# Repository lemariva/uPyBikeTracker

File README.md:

# uPyBikeTracker

## Main Hardware Components
| Part  | Description |  Qty |
|-:|-:|-:|
| [Wemos ESP32 Lora Board](https://www.banggood.com/2Pcs-Wemos-TTGO-LORA32-868915Mhz-ESP32-LoRa-OLED-0_96-Inch-Blue-Display-p-1239769.html?p=QW0903761303201409LG) | ESP32 + SSD1306 + SX1276 + CP2102| x1 |
| [GPS NEO7M](https://www.banggood.com/Ublox-NEO-7M-Flight-Controller-GPS-Module-Built-in-Data-Memory-p-973621.html?p=QW0903761303201409LG) / [GPS NEO6M](https://www.banggood.com/GY-NEO6MV2-New-NEO-6M-GPS-Module-NEO6MV2-with-Flight-Control-EEPROM-MWC-APM2_5-Large-Antenna-p-1348935.html?p=QW0903761303201409LG) | GPS Module| x1|
|[MPU9250/5](https://www.banggood.com/MPU-9250-GY-9250-9-Axis-Sensor-Module-I2C-SPI-Communication-Board-For-Arduino-p-1227241.html?p=QW0903761303201409LG)| IMU 10DOF Sensor| x1 |
|[IRLML2502](https://www.ebay.de/itm/20PCS-IRLML2502-ORIGINAL-MOSFET-N-CH-20V-4-2A-SOT-23-/162711066575) | MOSFETs | x4 | 
|[BME680](https://www.banggood.com/CJMCU-680-BME680-BOSCH-Temperature-And-Humidity-Pressure-Sensor-p-1268323.html?p=QW0903761303201409LG)| Atmospheric Pressure Sensor| x 1|
|[BQ27510-G3](http://www.ti.com/product/bq27510-g3/description) | Fuel Gauge |x1|
|[Lipo-Battery](https://www.banggood.com/ZOP-Power-3_7V-850mAh-1S-25C-Lipo-Battery-p-1013586.html?p=QW0903761303201409LG)| Battery| x1|
|[RTC Clock](https://www.conrad.de/de/ds1339u-33-tr-rtc-clockcalendar-i2c-interface-msop8-800202661.html)| Clock| x1 |
|[CR1220](https://www.conrad.de/de/knopfzellenhalter-1-cr-1216-cr-1220-horizontal-oberflaechenmontage-smd-l-x-b-x-h-1892-x-1207-x-318-mm-keystone-300-651317.html)| Battery Socket| x1 |
|[SIL Socket Row Strip PCB Connector](https://www.banggood.com/5-Pair-40-Pin-2_54mm-Male-Female-SIL-Socket-Row-Strip-PCB-Connector-p-953486.html?p=QW0903761303201409LG)| SIL Socket Row Strip PCB Connector | x1|
|[SMD Tact Push Buttons](https://www.banggood.com/100pcs-3-x-6-x-2_5mm-DC-12V-0_5A-SMD-Tact-Push-Button-Switch-p-1202259.html?p=QW0903761303201409LG)| Buttons| x4|
|[bq51013B](http://www.ti.com/product/BQ51013B/technicaldocuments)|  Highly Integrated Wireless Receiver Qi| x1|

## More Info
More info coming soon on [lemariva.com](https://lemariva.com).

## Revision
* 1.3v added wireless charging (not revised yet)
* 1.2v breakout boards integrated to the main board
* 1.1v added RTC Clock (DS1339)
* 1.0v initial commit

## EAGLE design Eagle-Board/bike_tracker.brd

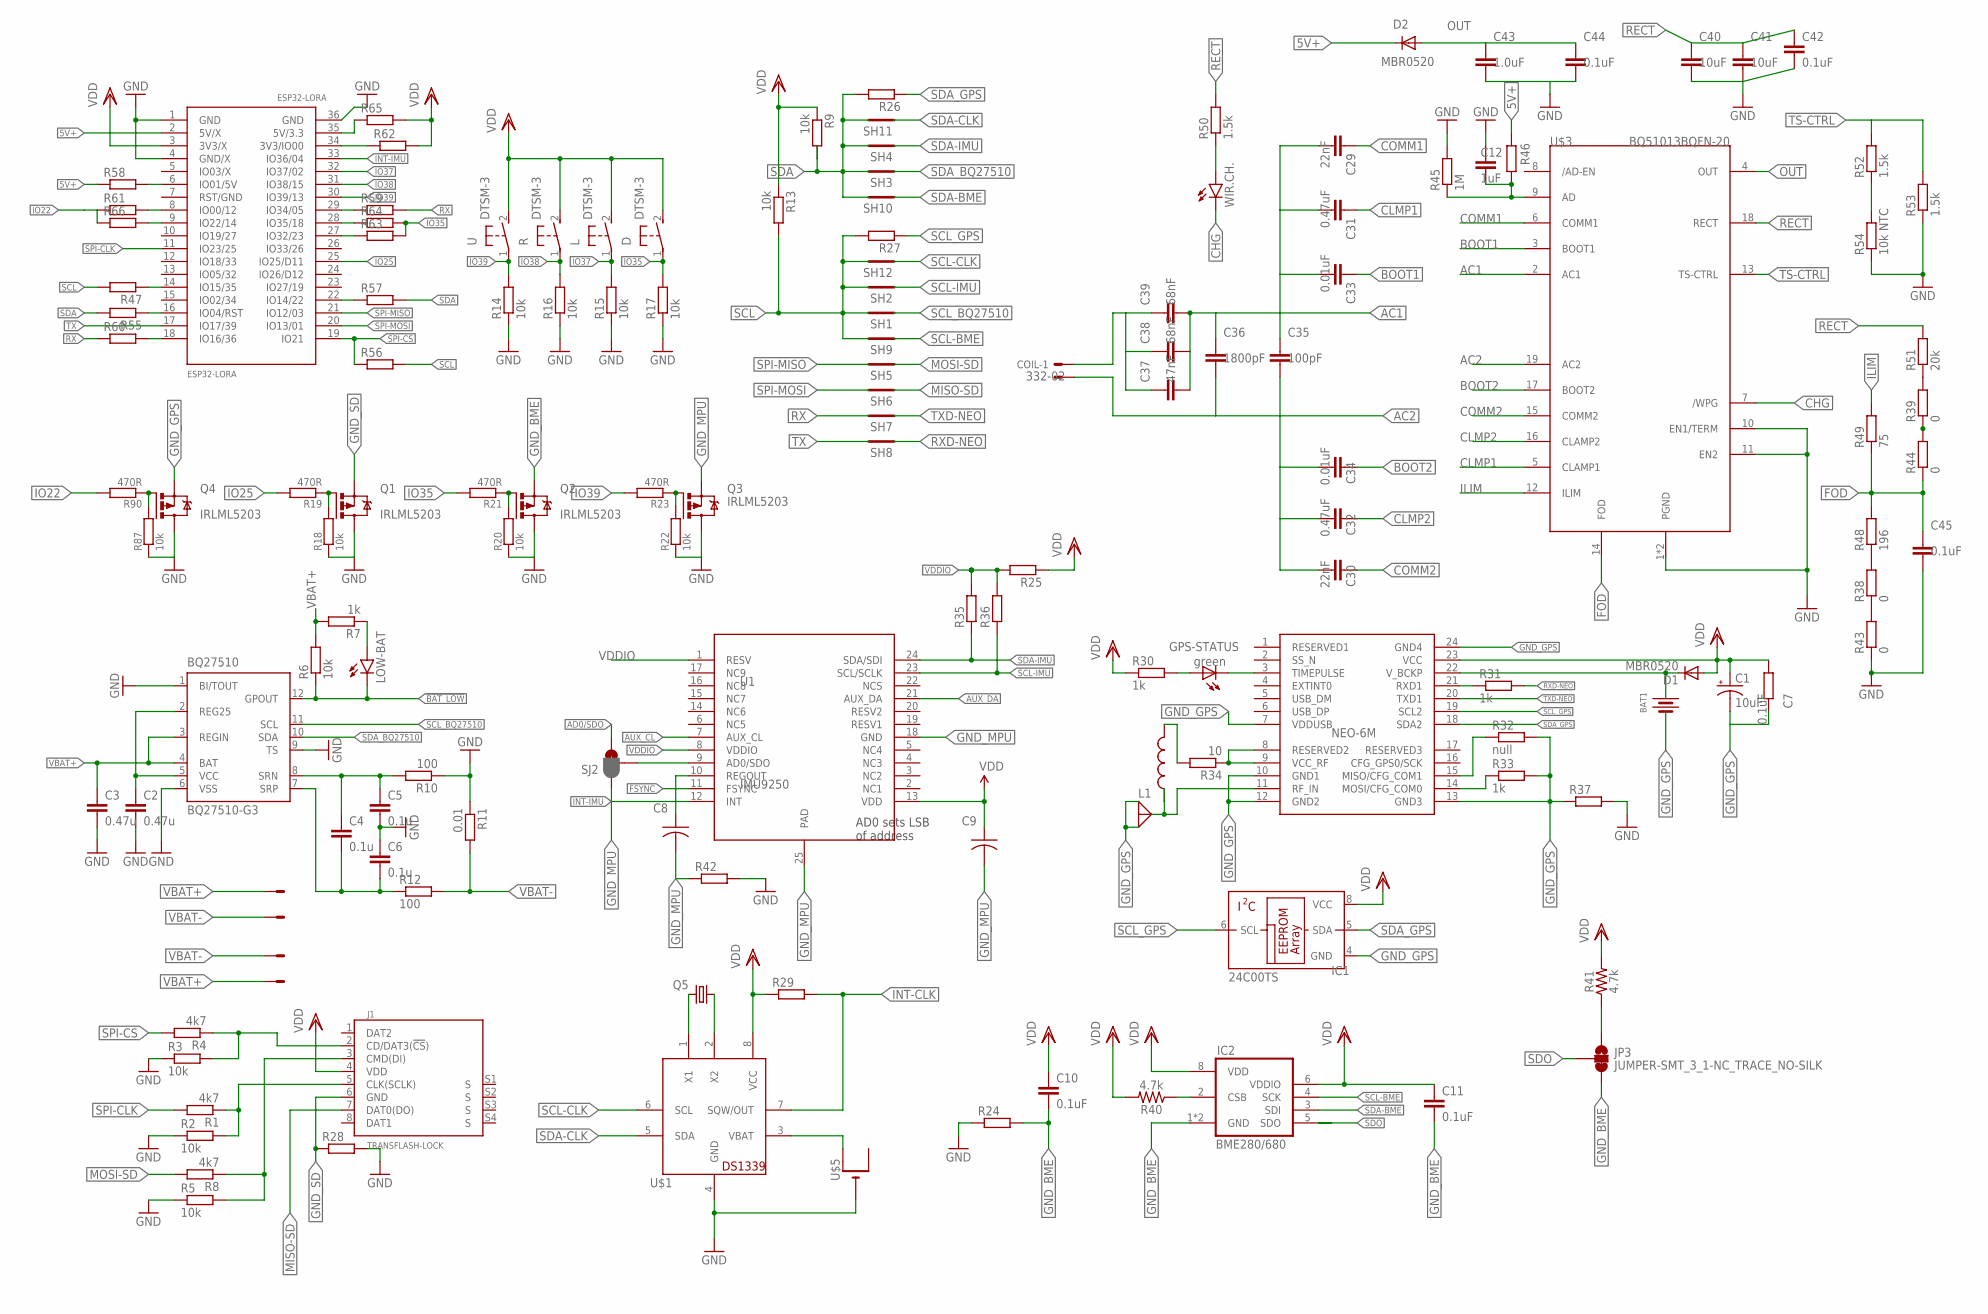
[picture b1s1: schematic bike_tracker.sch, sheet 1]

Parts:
BAT: 332-02
BAT1: XH414; TS414H
BAT-IN: 332-02
BQ27510: BQ27510-G3; DRZ
C1: 10uF; EIA3528
C2, C3: 0.47u; C0603
C4, C5, C6: 0.1u; C0603
C7: 0.1uF; R0603
C8, C9: 0.1uF; C0603K
C10, C11: 0.1uF; 0603
C12: 1uF; C0603
C29, C30: 22nF; C0603
C31, C32: 0.47uF; C0603
C33, C34: 0.01uF; C0603
C35: 100pF; C0603
C36: 1800pF; C0603
C37: 47nF; C0603
C38, C39: 68nF; C0603
C40, C41: 10uF; C0603
C42, C44, C45: 0.1uF; C0603
C43: 1.0uF; C0603
COIL: 332-02
D: DTSM-3
D1, D2: MBR0520; SOD123
ESP32-LORA: ESP32LORA; ESP32-LORA-TTGO
GPS-STATUS: green; 0805-LED
IC1: 24C00TS; TSSOP8
IC2: BME280/680; BME280
IPEX: ANT-UMCC; UMCC
J1: TRANSFLASH-LOCK; TRANSFLASH-LOCK-SOCK
JP3: JUMPER-SMT_3_1-NC_TRACE_NO-SILK; SMT-JUMPER_3_1-NC_TRACE_NO-SILK
L: DTSM-3
L1: INDUCTOR0603; 0603
LOW-BAT: LEDSML0805; SML0805
NEO-GPS: BLOX-NEO-6M; NE0-6M
Q1, Q2, Q3, Q4: IRLML5203; MICRO3
Q5: CRYSTALTC26H; TC26H
R: DTSM-3
R1, R4, R8: 4k7; R0603
R2, R3, R5, R6, R9, R13, R14, R15, R16, R17, R18, R20, R22, R87: 10k; R0603
R7, R30, R31, R33: 1k; R0603
R10, R12: 100; R0603
R11: 0.01; R0603
R19, R21, R23, R90: 470R; R0603
R24, R25, R26, R27, R28, R37, R42, R46, R47, R55, R56, R57, R58, R59, R60, R61, R62, R63, R64, R65, R66: R-EU_R0201; R0201
R29: R-EU_R0603; R0603
R32: null; R0603
R34: 10; R0603
R35, R36: 10K; R0603
R38, R39, R43, R44: 0; R0603
R40, R41: 4.7k; 0603
R45: 1M; R0603
R48: 196; R0603
R49: 75; R0603
R50, R52, R53: 1.5k; R0603
R51: 20k; R0603
R54: 10k NTC; R0603
SH1, SH2, SH3, SH4, SH5, SH6, SH7, SH8, SH9, SH10, SH11, SH12: SHORT; SHORT_TOP-20
SJ2: JUMPER_PAD-3-1&2_NC_BY_PASTE; PAD-HUMPER-3-1&2_NC_BY_PASTE_YES_SILK_FULL_BOX
U: DTSM-3
U1: IMU9250; LEAD-QFN24
U$1: DS1339; SOPM08
U$3: BQ51013BQFN-20; R-PVQFN-N20
U$5: CR1220SMT; CR1220-SMD
WIR.CH.: LEDSML0805; SML0805

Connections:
5V+: D2.C, ESP32-LORA.2 (5V/X), R46.2, R58.1
!BAT_LOW: BQ27510.12 (GPOUT), LOW-BAT.C, R6.1
AC1: C29.2, C31.1, C33.1, C35.1, C36.1, C37.2, C38.2, C39.2, U$3.2 (AC1)
AC1'1: C37.1, C38.1, C39.1, COIL.1
AC2: C30.1, C32.1, C34.1, C35.2, C36.2, COIL.2, U$3.19 (AC2)
AD0/SDO: SJ2.3
AUX_CL: U1.7 (AUX_CL)
AUX_DA: U1.21 (AUX_DA)
BOOT1: C33.2, U$3.3 (BOOT1)
BOOT2: C34.2, U$3.17 (BOOT2)
CHG: U$3.7 (/WPG), WIR.CH..C
CLMP1: C31.2, U$3.5 (CLAMP1)
CLMP2: C32.2, U$3.16 (CLAMP2)
COMM1: C29.1, U$3.6 (COMM1)
COMM2: C30.2, U$3.15 (COMM2)
FOD: C45.1, R44.1, R48.2, R49.1, U$3.14 (FOD)
FSYNC: U1.11 (FSYNC)
GND: BQ27510.1 (BI/TOUT), BQ27510.6 (VSS), BQ27510.9 (TS), C2.2, C3.2, C5.2, C6.1, C12.1, C40.2, C41.2, C42.2, C43.2, C44.2, C45.2, ESP32-LORA.1 (GND), ESP32-LORA.4 (GND/X), ESP32-LORA.36 (GND), Q1.3 (D), Q2.3 (D), Q3.3 (D), Q4.3 (D), R2.1, R3.1, R5.1, R10.1, R11.1, R14.1, R15.1, R16.1, R17.1, R18.1, R20.1, R22.1, R24.1, R28.2, R37.2, R42.2, R43.1, R45.2, R53.1, R54.1, R87.1, U$1.4 (GND), U$3.1 (PGND), U$3.10 (EN1/TERM), U$3.11 (EN2), U$3.20 (PGND), U$5.-
GND_BME: C10.2, C11.2, IC2.1 (GND), IC2.7 (GND), JP3.3, Q2.2 (S), R24.2
GND_GPS: BAT1.2 (-), C1.C (-), C7.2, IC1.4 (GND), IPEX.1 (GND1), IPEX.2 (GND2), NEO-GPS.7 (VDDUSB), NEO-GPS.10 (GND1), NEO-GPS.12 (GND2), NEO-GPS.13 (GND3), NEO-GPS.24 (GND4), Q4.2 (S), R32.2, R33.2, R37.1
GND_MPU: C8.2, C9.2, Q3.2 (S), R42.1, SJ2.1, U1.18 (GND), U1.25 (PAD)
GND_SD: J1.6 (GND), Q1.2 (S), R28.1
ILIM: R49.2, U$3.12 (ILIM)
INT-CLK: R29.2, U$1.7 (SQW/OUT)
INT-IMU: ESP32-LORA.33 (IO36/04), U1.12 (INT)
IO22: R61.1, R66.1, R90.2
IO25: ESP32-LORA.25 (IO25/D11), R19.2
IO35: D.1, R17.2, R21.2, R63.2, R64.2
IO37: ESP32-LORA.32 (IO37/02), L.1, R15.2
IO38: ESP32-LORA.31 (IO38/15), R.1, R16.2
IO39: ESP32-LORA.30 (IO39/13), R14.2, R23.2, U.1
MISO-SD: J1.7 (DAT0(DO)), SH6.1
MOSI-SD: R8.2, SH5.1
unnamed: J1.5 (CLK(SCLK)), R1.1, R2.2
unnamed: J1.2 (CD/DAT3(!CS!)), R3.2, R4.1
unnamed: J1.3 (CMD(DI)), R5.2, R8.1
unnamed: Q4.1 (G), R87.2, R90.1
unnamed: Q1.1 (G), R18.2, R19.1
unnamed: Q2.1 (G), R20.2, R21.1
unnamed: BQ27510.2 (REG25), BQ27510.5 (VCC), C2.1
unnamed: Q3.1 (G), R22.2, R23.1
unnamed: LOW-BAT.A, R7.1
unnamed: Q5.1, U$1.2 (X2)
unnamed: BQ27510.8 (SRN), C4.1, C5.1, R10.2
unnamed: ESP32-LORA.6 (IO01/5V), R58.2
unnamed: Q5.2, U$1.1 (X1)
unnamed: BQ27510.7 (SRP), C4.2, C6.2, R12.1
unnamed: U$1.3 (VBAT), U$5.+$1 (+)
unnamed: GPS-STATUS.A, R30.2
unnamed: GPS-STATUS.C, NEO-GPS.3 (TIMEPULSE)
unnamed: IPEX.3 (ANT), L1.1, NEO-GPS.11 (RF_IN)
unnamed: NEO-GPS.21 (RXD1), R31.1
unnamed: NEO-GPS.15 (MISO/CFG_COM1), R32.1
unnamed: NEO-GPS.14 (MOSI/CFG_COM0), R33.1
unnamed: BAT1.1 (+), D1.C, NEO-GPS.22 (V_BCKP)
unnamed: L1.2, R34.2
unnamed: NEO-GPS.8 (RESERVED2), NEO-GPS.9 (VCC_RF), R34.1
unnamed: IC2.2 (CSB), R40.1
unnamed: JP3.1, R41.1
unnamed: SJ2.2, U1.9 (AD0/SDO)
unnamed: R38.2, R48.1
unnamed: R39.2, R51.1
unnamed: R50.1, WIR.CH..A
unnamed: R52.1, R54.2
unnamed: C12.2, R45.1, R46.1, U$3.9 (AD)
unnamed: R38.1, R43.2
unnamed: R39.1, R44.2
unnamed: ESP32-LORA.14 (IO15/35), R47.1
unnamed: ESP32-LORA.16 (IO04/RST), R55.1
unnamed: ESP32-LORA.22 (IO14/22), R57.1
unnamed: ESP32-LORA.29 (IO34/05), R59.1
unnamed: ESP32-LORA.18 (IO16/36), R60.2
unnamed: ESP32-LORA.34 (3V3/IO00), R62.1
unnamed: ESP32-LORA.8 (IO00/12), R61.2
unnamed: ESP32-LORA.35 (5V/3.3), R65.1
unnamed: ESP32-LORA.28 (IO35/18), R64.1
unnamed: ESP32-LORA.9 (IO22/14), R66.2
unnamed: ESP32-LORA.27 (IO32/23), R63.1
OUT: C43.1, C44.1, D2.A, U$3.4 (OUT)
PWPD: BQ27510.EXP@1 (PWPD), BQ27510.EXP@2 (PWPD), BQ27510.EXP@3 (PWPD), BQ27510.EXP@4 (PWPD), BQ27510.EXP@5 (PWPD), BQ27510.EXP@6 (PWPD), BQ27510.EXP@7 (PWPD), BQ27510.EXP@8 (PWPD), BQ27510.EXP@9 (PWPD)
RECT: C40.1, C41.1, C42.1, R50.2, R51.2, U$3.18 (RECT)
REGOUT: C8.1, U1.10 (REGOUT)
RX: R59.2, R60.1, SH7.2
RXD-NEO: R31.2, SH8.1
SCL: R13.2, R27.2, R47.2, R56.2, SH1.2, SH2.2, SH9.2, SH12.2
SCL-BME: IC2.4 (SCK), SH9.1
SCL-CLK: SH12.1, U$1.6 (SCL)
SCL-IMU: R36.1, SH2.1, U1.23 (SCL/SCLK)
SCL_BQ27510: BQ27510.11 (SCL), SH1.1
SCL_GPS: IC1.6 (SCL), NEO-GPS.19 (SCL2), R27.1
SDA: R9.2, R26.2, R55.2, R57.2, SH3.2, SH4.2, SH10.2, SH11.2
SDA-BME: IC2.3 (SDI), SH10.1
SDA-CLK: SH11.1, U$1.5 (SDA)
SDA-IMU: R35.1, SH4.1, U1.24 (SDA/SDI)
SDA_BQ27510: BQ27510.10 (SDA), SH3.1
SDA_GPS: IC1.5 (SDA), NEO-GPS.18 (SDA2), R26.1
SDO: IC2.5 (SDO), JP3.2
SPI-CLK: ESP32-LORA.11 (IO23/25), R1.2
SPI-CS: ESP32-LORA.19 (IO21), R4.2, R56.1
SPI-MISO: ESP32-LORA.21 (IO12/03), SH5.2
SPI-MOSI: ESP32-LORA.20 (IO13/01), SH6.2
TS-CTRL: R52.2, R53.2, U$3.13 (TS-CTRL)
TX: ESP32-LORA.17 (IO17/39), SH8.2
TXD-NEO: NEO-GPS.20 (TXD1), SH7.1
VBAT+: BAT.1, BAT-IN.1, BQ27510.3 (REGIN), BQ27510.4 (BAT), C3.1, R6.2, R7.2
VBAT-: BAT.2, BAT-IN.2, R11.2, R12.2
VDD: C1.A (+), C7.1, C9.1, C10.1, C11.1, D.2, D1.A, ESP32-LORA.3 (3V3/X), IC1.8 (VCC), IC2.6 (VDDIO), IC2.8 (VDD), J1.4 (VDD), L.2, NEO-GPS.23 (VCC), R.2, R9.1, R13.1, R25.1, R29.1, R30.1, R40.2, R41.2, R62.2, R65.2, U.2, U1.13 (VDD), U$1.8 (VCC)
VDDIO: R25.2, R35.2, R36.2, U1.1 (RESV), U1.8 (VDDIO)

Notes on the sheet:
AD0 sets LSB of address

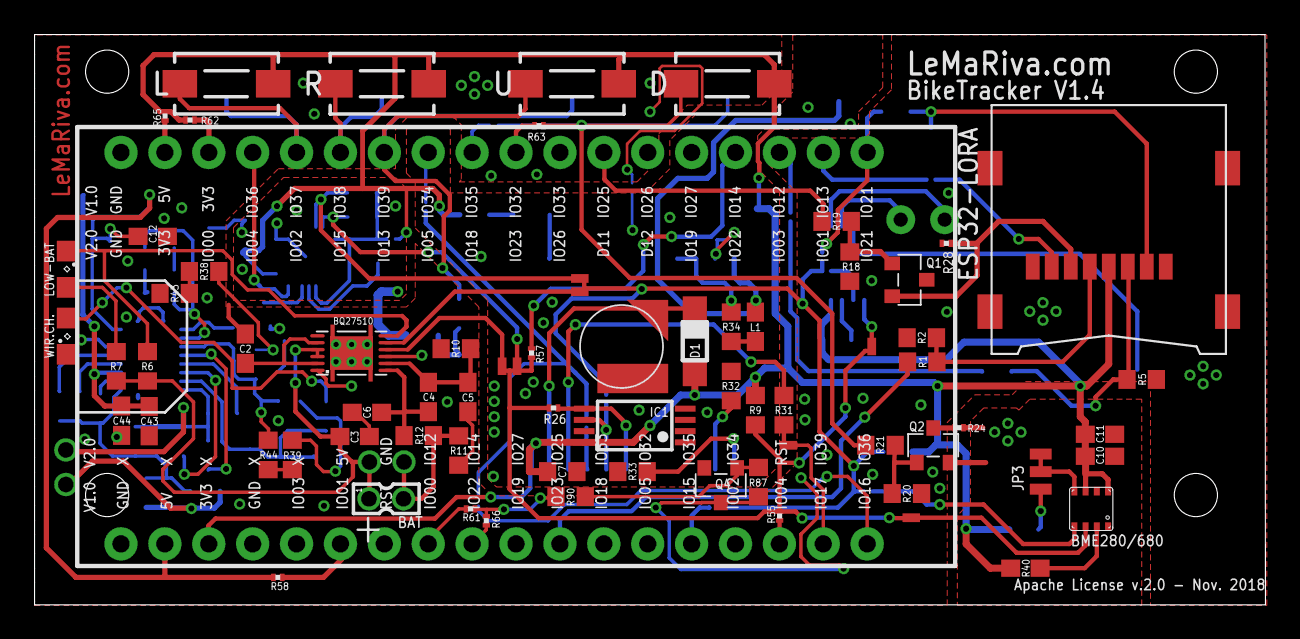
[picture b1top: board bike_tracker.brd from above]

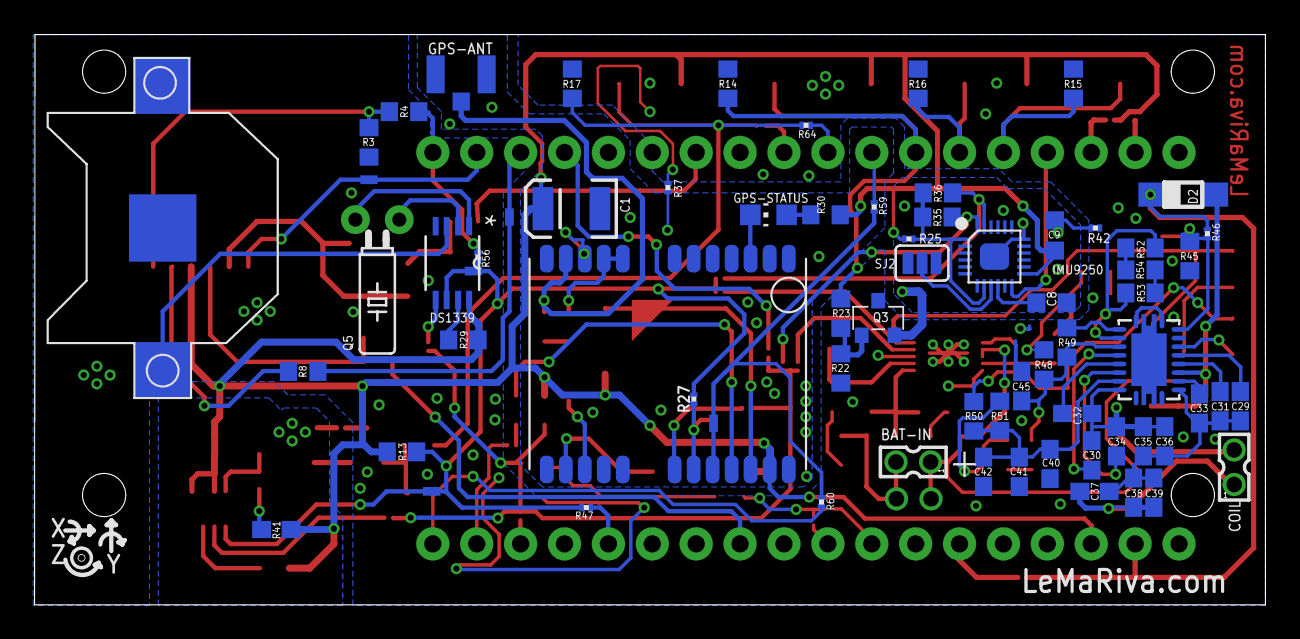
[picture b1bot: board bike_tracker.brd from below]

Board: 2 copper layers, 71.2 x 33.0 mm, 141 parts (69 on the bottom side), 104 nets.

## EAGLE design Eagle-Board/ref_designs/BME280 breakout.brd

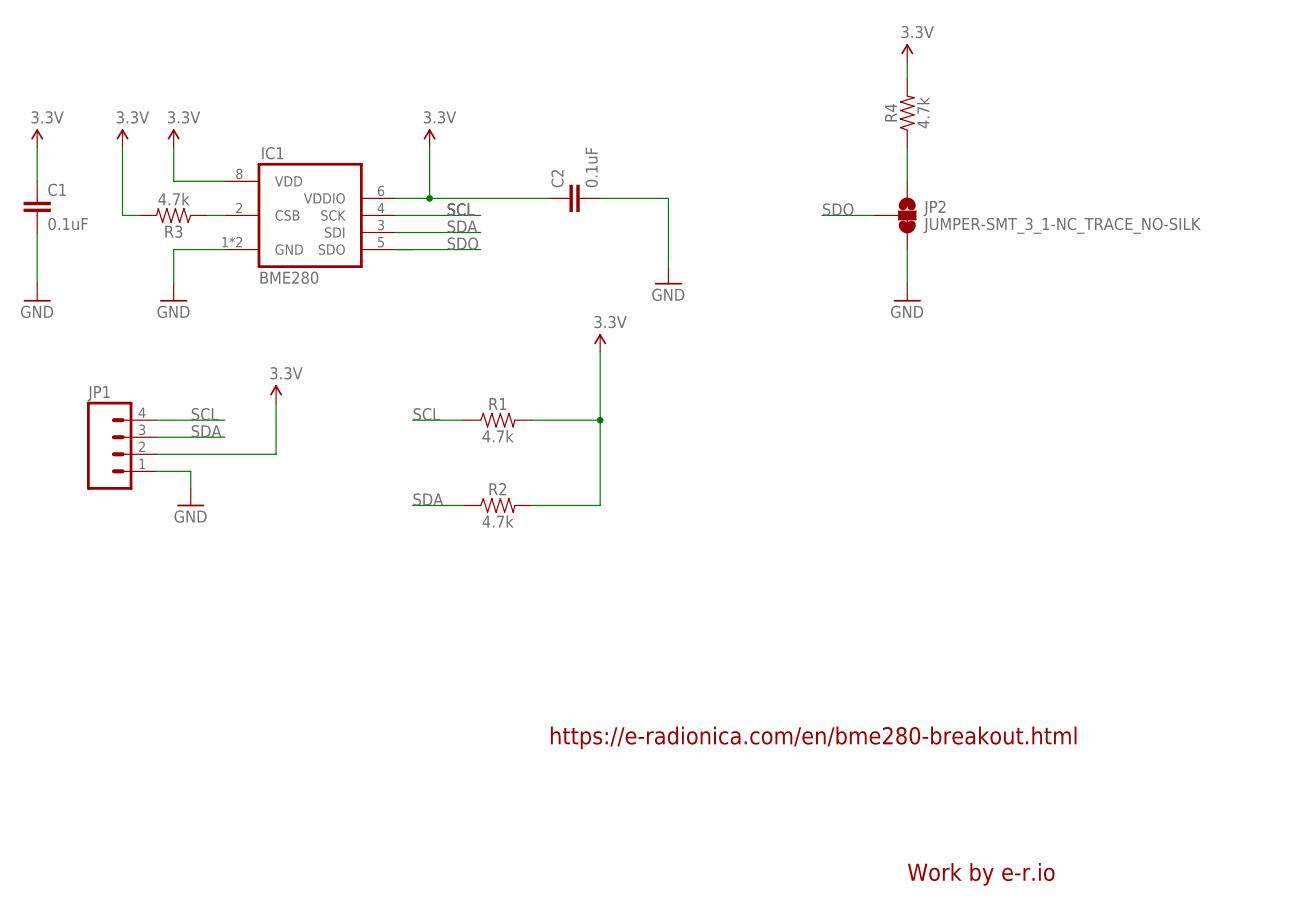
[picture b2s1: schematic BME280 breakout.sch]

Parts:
C1, C2: 0.1uF; 0603
IC1: BME280
JP1: M04PTH; 1X04
JP2: JUMPER-SMT_3_1-NC_TRACE_NO-SILK; SMT-JUMPER_3_1-NC_TRACE_NO-SILK
R1, R2, R3, R4: 4.7k; 0603

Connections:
3.3V: C1.1, C2.1, IC1.6 (VDDIO), IC1.8 (VDD), JP1.2, R1.2, R2.2, R3.2, R4.2
GND: C1.2, C2.2, IC1.1 (GND), IC1.7 (GND), JP1.1, JP2.3
unnamed: IC1.2 (CSB), R3.1
unnamed: JP2.1, R4.1
SCL: IC1.4 (SCK), JP1.4, R1.1
SDA: IC1.3 (SDI), JP1.3, R2.1
SDO: IC1.5 (SDO), JP2.2

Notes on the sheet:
https://e-radionica.com/en/bme280-breakout.html
Work by e-r.io

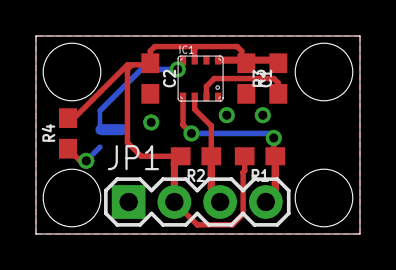
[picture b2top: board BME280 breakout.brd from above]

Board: 2 copper layers, 18.0 x 11.0 mm, 11 parts (1 on the bottom side), 7 nets.

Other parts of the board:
U$1: OSH3MM
U$2: NOVI_LOGO-4MM

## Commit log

2018-09-30 work in progress - only a backup
2018-10-01 files moved to folder
2018-10-01 added eagle board for bike tracker - work in progress
2018-10-01 board design ready - revising and exporting for gerber - SeeedStudio Fusion files added
2018-10-01 libraries updated
2018-10-01 texas and switch libraries added final version with buttons and possibility to switch off/on external devices
2018-10-01 minor modifications made
2018-10-03 added main hardware component list
2018-10-20 updated rev1.1 -> added RTC chip (DS1339)
2018-10-24 revision v1.2
2018-10-24 first commit rev1.2
2018-10-24 minor modifications
2018-10-24 rules deleted
2018-10-26 modified and cleaned for production
2018-10-26 last minute modifications added
2018-10-28 Update README.md
    BME280 changed with a BME680
2018-11-23 wireless charging option added
2018-11-24 added compatibility with TTGO LoRa v2.0
2018-11-24 minor error correction and exported for production!

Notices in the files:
Eagle-Board/bike_tracker.brd:
Apache License v.2.0 - Nov. 2018
parts and their libraries:
SparkFun-Capacitors: Licensing: Creative Commons ShareAlike 4.0 International - https://creativecommons.org/licenses/by-sa/4.0
SparkFun: Licensing: CC v3.0 Share-Alike You are welcome to use this library for commercial purposes.
